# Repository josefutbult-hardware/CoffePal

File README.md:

# CoffeePal

_Upbeat music starts_.

Have YOU ever forgotten a cup of coffee for too long when working on a project, resulting in a cold cup of liquid sadness? Then the _Coffee Pal_ is for YOU!

Jokes aside, even though I'm one of those sadistic people who enjoy cold coffee, this actually is a bit of a problem for me. It is an even bigger problem for my mum, who regulary walks away from her cups. The idea with the Coffee Pal is to have a little gadget that you can clip onto a cup. This will then sense when a cup has been stationary for too long, and then starts to make a noise to remind you to drink from it. This will continue periodically until the cup has been moved, and hopefully has been drunk from. There is also a light sensor on there that will disable the notification if the room is too dark, to make sure it won't wake you up in the middle of the night if you've forgotten it. Everything is on a small PCB that runs on a coin cell battery, and with a plastic clamp to fasten it to the cup.

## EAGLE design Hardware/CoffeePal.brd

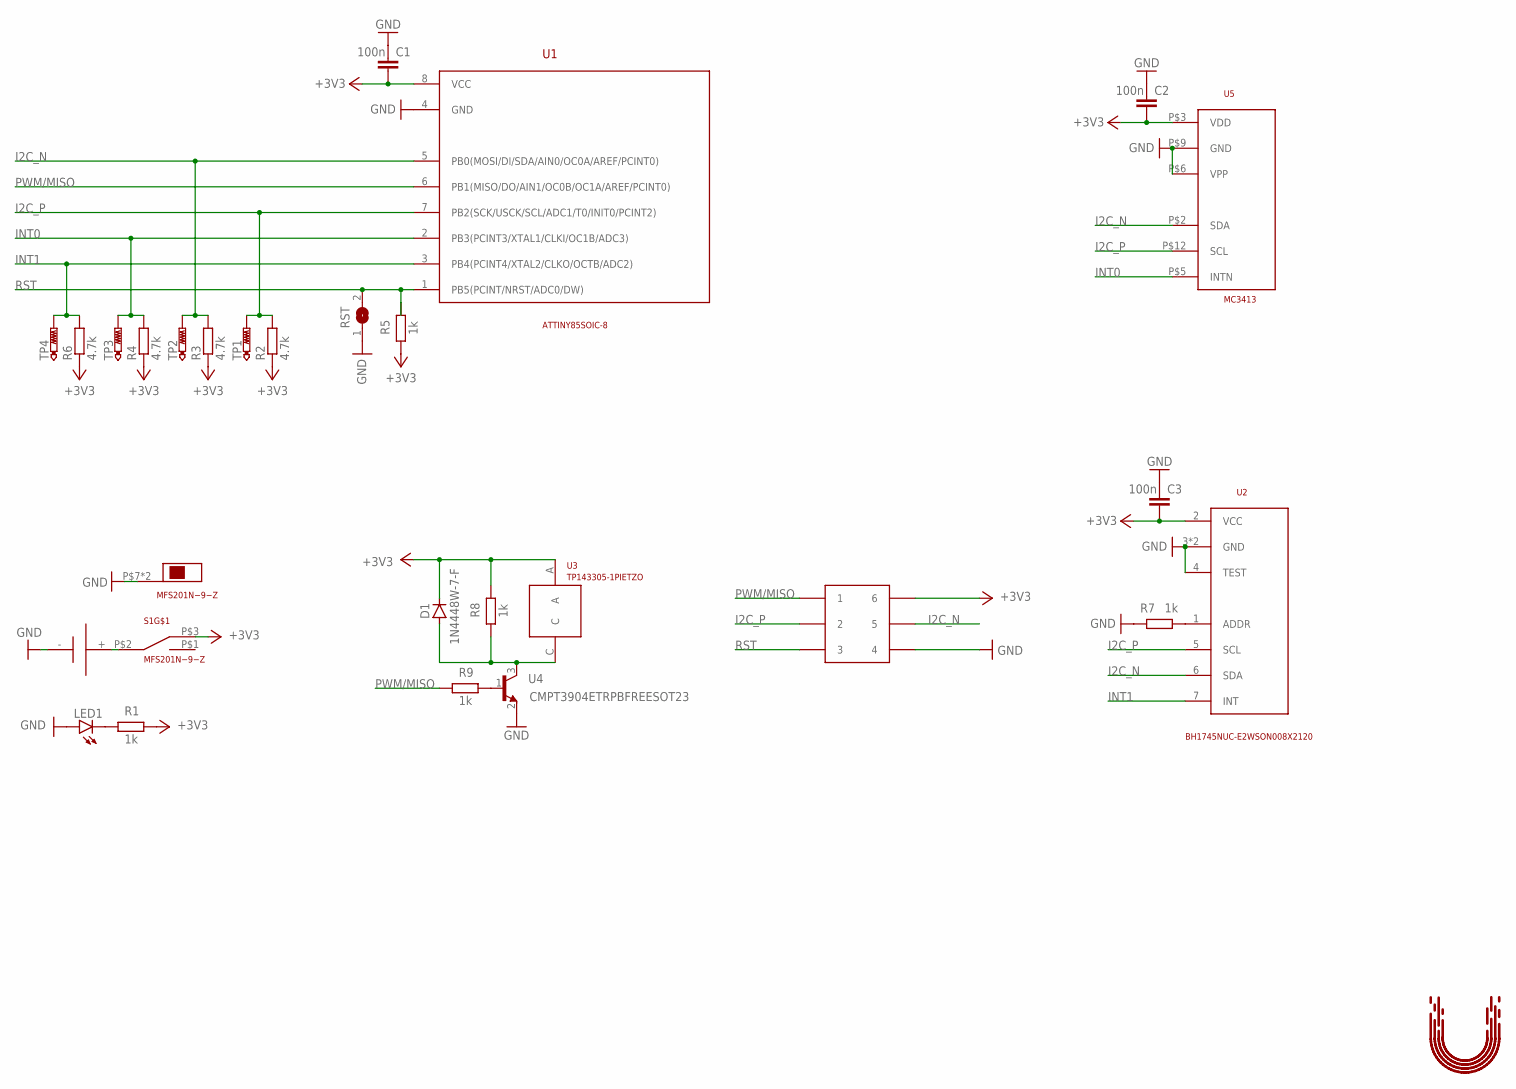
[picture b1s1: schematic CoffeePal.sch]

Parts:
C1, C2, C3: 100n; 0603
D1: 1N4448W-7-F; SOD-123_MINI-SMA; MPN 1N4448W-7-F
LED1: LEDLED_1206; DIOC3216X75N
PROGRAM: 3X2_PINHEADER3X2_PINHEADER; HDRV6W64P254_2X3_900X508X838B
R1, R5, R7, R8, R9: 1k; R0603
R2, R3, R4, R6: 4.7k; R0603
RST: JUMPER; SJ
S1: MFS201N−9−Z; MFS201N-9-Z
TP1, TP2, TP3, TP4: PTR1B1,27; B1,27
U1: ATTINY85SOIC-8; SOIC127P798X216-8N
U2: BH1745NUC-E2WSON008X2120; SON50P210X200X60-9T75X150N
U3: TP143305-1PIETZO; SODFL151143X1070N
U4: CMPT3904ETRPBFREESOT23; SOT95P240X110-3N
U5: MC3413; VLGA-12
U$2: 1061TR
U$3: UTBULT_DESIGN1; UD_1

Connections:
+3V3: C1.2, C2.2, C3.2, D1.C, PROGRAM.6, R1.2, R2.1, R3.1, R4.1, R5.1, R6.1, R8.2, S1.P$3, U1.8 (VCC), U2.2 (VCC), U3.A, U5.P$3 (VDD)
GND: C1.1, C2.1, C3.1, LED1.A, PROGRAM.4, R7.1, RST.1, S1.P$7, S1.P$8, U1.4 (GND), U2.3 (GND), U2.4 (TEST), U2.9 (GND), U4.2 (E), U5.P$6 (VPP), U5.P$9 (GND), U$2.-
I2C_N: PROGRAM.5, R3.2, TP2.TP, U1.5 (PB0(MOSI/DI/SDA/AIN0/OC0A/AREF/PCINT0)), U2.6 (SDA), U5.P$2 (SDA)
I2C_P: PROGRAM.2, R2.2, TP1.TP, U1.7 (PB2(SCK/USCK/SCL/ADC1/T0/INIT0/PCINT2)), U2.5 (SCL), U5.P$12 (SCL)
INT0: R4.2, TP3.TP, U1.2 (PB3(PCINT3/XTAL1/CLKI/OC1B/ADC3)), U5.P$5 (INTN)
INT1: R6.2, TP4.TP, U1.3 (PB4(PCINT4/XTAL2/CLKO/OCTB/ADC2)), U2.7 (INT)
unnamed: S1.P$2, U$2.+
unnamed: LED1.C, R1.1
unnamed: R7.2, U2.1 (ADDR)
unnamed: R9.2, U4.1 (B)
unnamed: D1.A, R8.1, U3.C, U4.3 (C)
PWM/MISO: PROGRAM.1, R9.1, U1.6 (PB1(MISO/DO/AIN1/OC0B/OC1A/AREF/PCINT0))
RST: PROGRAM.3, R5.2, RST.2, U1.1 (PB5(PCINT/NRST/ADC0/DW))

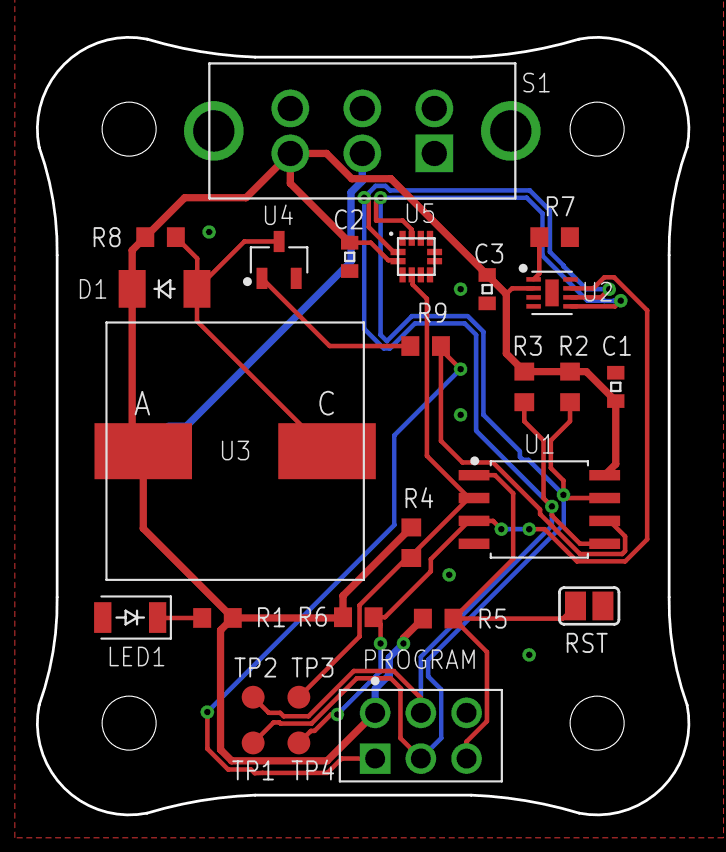
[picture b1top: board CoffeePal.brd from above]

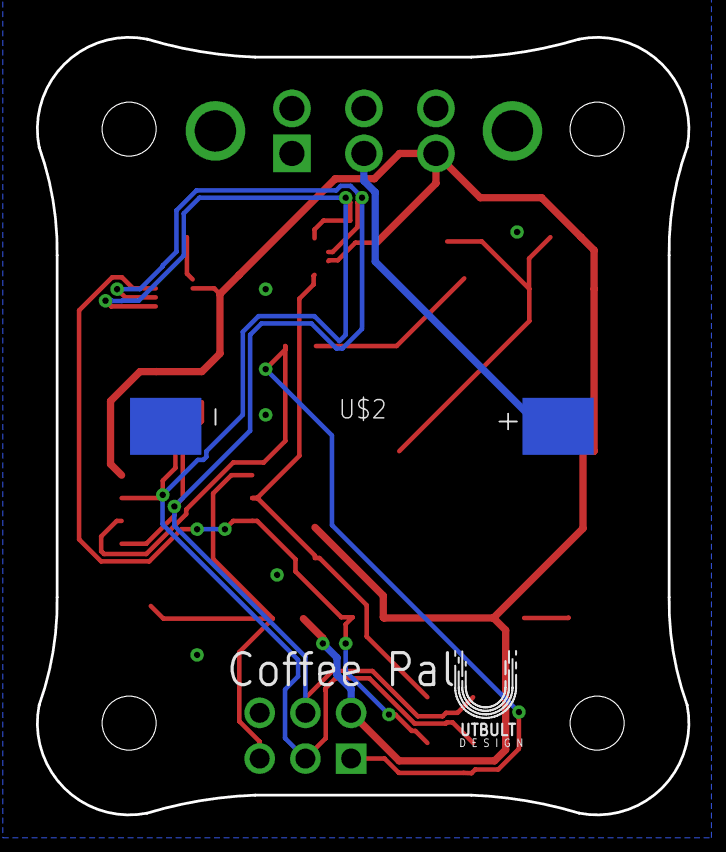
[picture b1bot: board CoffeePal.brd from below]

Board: 2 copper layers, 36.2 x 43.2 mm, 28 parts (2 on the bottom side), 13 nets.

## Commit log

2021-05-16 Init
2021-05-16 Drew traces and created boom
2021-05-17 Checked spelling of README.md
